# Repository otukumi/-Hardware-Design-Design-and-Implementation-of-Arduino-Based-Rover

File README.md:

# Hardware-Design/Design and Implementation of Arduino Based Rover

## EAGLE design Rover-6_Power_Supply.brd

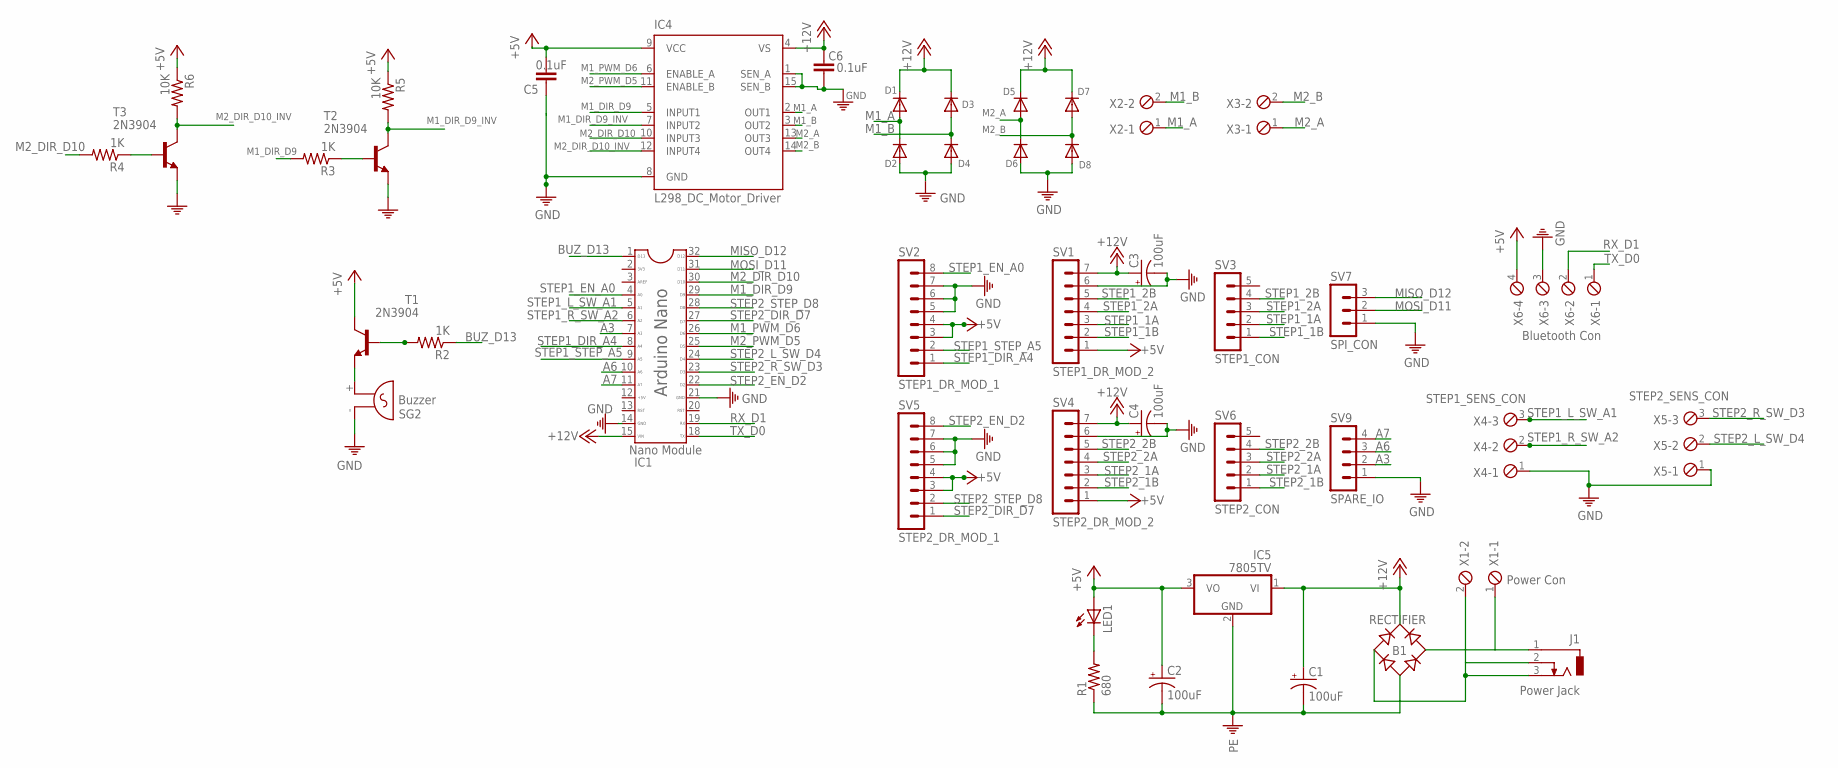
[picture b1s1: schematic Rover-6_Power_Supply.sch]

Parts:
B1: RECTIFIER; RB1A
C1, C2, C3, C4: 100uF; E1,8-4
C5, C6: 0.1uF; C025-024X044
D1, D2, D3, D4, D5, D6, D7, D8: DIODE-D-2.5; D-2.5
IC1: Nano Module; DIL32
IC4: L298_DC_Motor_Driver; MULTIWATT-15
IC5: 7805TV; TO220V
J1: Power Jack; ROVER-PW-JACL
LED1: LED3MM
R1: 680; 0204/5
R2, R3, R4: 1K; 0204/5
R5, R6: 10K; 0204/5
SG2: Buzzer; F/QMX
SV1: STEP1_DR_MOD_2; MA07-1
SV2: STEP1_DR_MOD_1; MA08-1
SV3: STEP1_CON; MA05-1
SV4: STEP2_DR_MOD_2; MA07-1
SV5: STEP2_DR_MOD_1; MA08-1
SV6: STEP2_CON; MA05-1
SV7: SPI_CON; MA03-1
SV9: SPARE_IO; MA04-1
T1, T2, T3: 2N3904; TO92
X1: Power Con; 2POL254
X2, X3: MPT2; 2POL254
X4: STEP1_SENS_CON; 3POL254
X5: STEP2_SENS_CON; 3POL254
X6: Bluetooth Con; 4POL254

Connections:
+5V: C2.+, C5.2, IC4.9 (VCC), IC5.3 (VO), LED1.A, R5.1, R6.1, SV1.1, SV2.3, SV2.4, SV4.1, SV5.3, SV5.4, T1.1 (C), X6.4
+12V: B1.+, C1.+, C3.+, C4.+, C6.2, D1.C, D3.C, D5.C, D7.C, IC1.15 (VIN), IC4.4 (VS), IC5.1 (VI), SV1.7, SV4.7
A3: IC1.7 (A3/D17), SV9.2
A6: IC1.10 (A6), SV9.3
A7: IC1.11 (A7), SV9.4
BUZ_D13: IC1.1 (D13), R2.1
M1_A: D1.A, D2.C, IC4.2 (OUT1), X2.1
M1_B: D3.A, D4.C, IC4.3 (OUT2), X2.2
M1_DIR_D9: IC1.29 (D9/PWM), IC4.5 (INPUT1), R3.2
M1_DIR_D9_INV: IC4.7 (INPUT2), R5.2, T2.1 (C)
M1_PWM_D6: IC1.26 (D6/PWM), IC4.6 (ENABLE_A)
M2_A: D5.A, D6.C, IC4.13 (OUT3), X3.1
M2_B: D7.A, D8.C, IC4.14 (OUT4), X3.2
M2_DIR_D10: IC1.30 (D10/PWM), IC4.10 (INPUT3), R4.2
M2_DIR_D10_INV: IC4.12 (INPUT4), R6.2, T3.1 (C)
M2_PWM_D5: IC1.25 (D5/PWM), IC4.11 (ENABLE_B)
MISO_D12: IC1.32 (D12/MISO), SV7.3
MOSI_D11: IC1.31 (D11/MOSI), SV7.2
unnamed: B1.AC1, J1.1, X1.1
unnamed: B1.AC2, J1.2, J1.3, X1.2
unnamed: LED1.K (C), R1.2
unnamed: R4.1, T3.2 (B)
unnamed: R3.1, T2.2 (B)
unnamed: SG2.+ (2), T1.3 (E)
unnamed: R2.2, T1.2 (B)
PE: B1.-, C1.-, C2.-, C3.-, C4.-, C5.1, C6.1, D2.A, D4.A, D6.A, D8.A, IC1.14 (GND1), IC1.21 (GND2), IC4.1 (SEN_A), IC4.8 (GND), IC4.15 (SEN_B), IC5.2 (GND), R1.1, SG2.- (1), SV1.6, SV2.5, SV2.6, SV2.7, SV4.6, SV5.5, SV5.6, SV5.7, SV7.1, SV9.1, T2.3 (E), T3.3 (E), X4.1, X5.1, X6.3
RX_D1: IC1.19 (RX), X6.2
STEP1_1A: SV1.3, SV3.2
STEP1_1B: SV1.2, SV3.1
STEP1_2A: SV1.4, SV3.3
STEP1_2B: SV1.5, SV3.4
STEP1_DIR_A4: IC1.8 (A4/D18/SDA), SV2.1
STEP1_EN_A0: IC1.4 (A0/D14), SV2.8
STEP1_L_SW_A1: IC1.5 (A1/D15), X4.3
STEP1_R_SW_A2: IC1.6 (A2/D16), X4.2
STEP1_STEP_A5: IC1.9 (A5/D19/SCL), SV2.2
STEP2_1A: SV4.3, SV6.2
STEP2_1B: SV4.2, SV6.1
STEP2_2A: SV4.4, SV6.3
STEP2_2B: SV4.5, SV6.4
STEP2_DIR_D7: IC1.27 (D7), SV5.1
STEP2_EN_D2: IC1.22 (D2), SV5.8
STEP2_L_SW_D4: IC1.24 (D4), X5.2
STEP2_R_SW_D3: IC1.23 (D3), X5.3
STEP2_STEP_D8: IC1.28 (D8), SV5.2
TX_D0: IC1.18 (TX), X6.1

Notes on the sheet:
D13
3V3
AREF
+5V
RST
GND
VIN
D10
D11
D12
Arduino Nano

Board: 2 copper layers, 44 parts (0 on the bottom side), 46 nets, no tracks yet.

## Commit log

2023-08-30 Add files via upload
    This the C++ code for the controlling the rover
2023-08-30 Add files via upload
    PCB Systematic Design Stages using Eagle software.
